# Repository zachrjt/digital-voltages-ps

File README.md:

# **Dual Fixed-Voltage Power Supply with V,I Readout**

## Background
The motivation behind this project was that in the past I have come across a need for a portable fixed-voltage 3.3V and 5V supplies. Specifically, I needed a supply that didn’t require me to set up a variable lab power supply while also being portable and rugged so that I could take it on the go.
Why did it end up taking on this *”polished”* look? I was looking to gain more SMD soldering experience and further my experience in PCB layout and schematic documentation. So, I approached this project in a more methodical, thorough-engineering manner than what I do typically for other personal projects of mine.
## Design and Construction
The main and display PCBs were captured and routed in KiCad, while the back and front enclosure panels were designed in Fusion 360. The code was, and is, written using the Arduino IDE and framework thanks only to the existence of the megaTinyCore library for 2-series attiny chips.
## Result
As seen in the picture above, the resulting power supply is certainly an *aesthetic*, but it is functional which is the most important thing. It took two PCB revisions of the main board because of wrong footprints for two resistors, and ~1 month of daily effort. There were many hours spent at my bench with an oscilloscope debugging my own oversights in the first PCB revision but I enjoyed every minute. The approach I took paid off since I've gained a lot of knowledge and experience where I wanted to, and the result is something I'm proud to share.

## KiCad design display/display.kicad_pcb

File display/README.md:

# Display Board Schematic, PCB, and Documentation

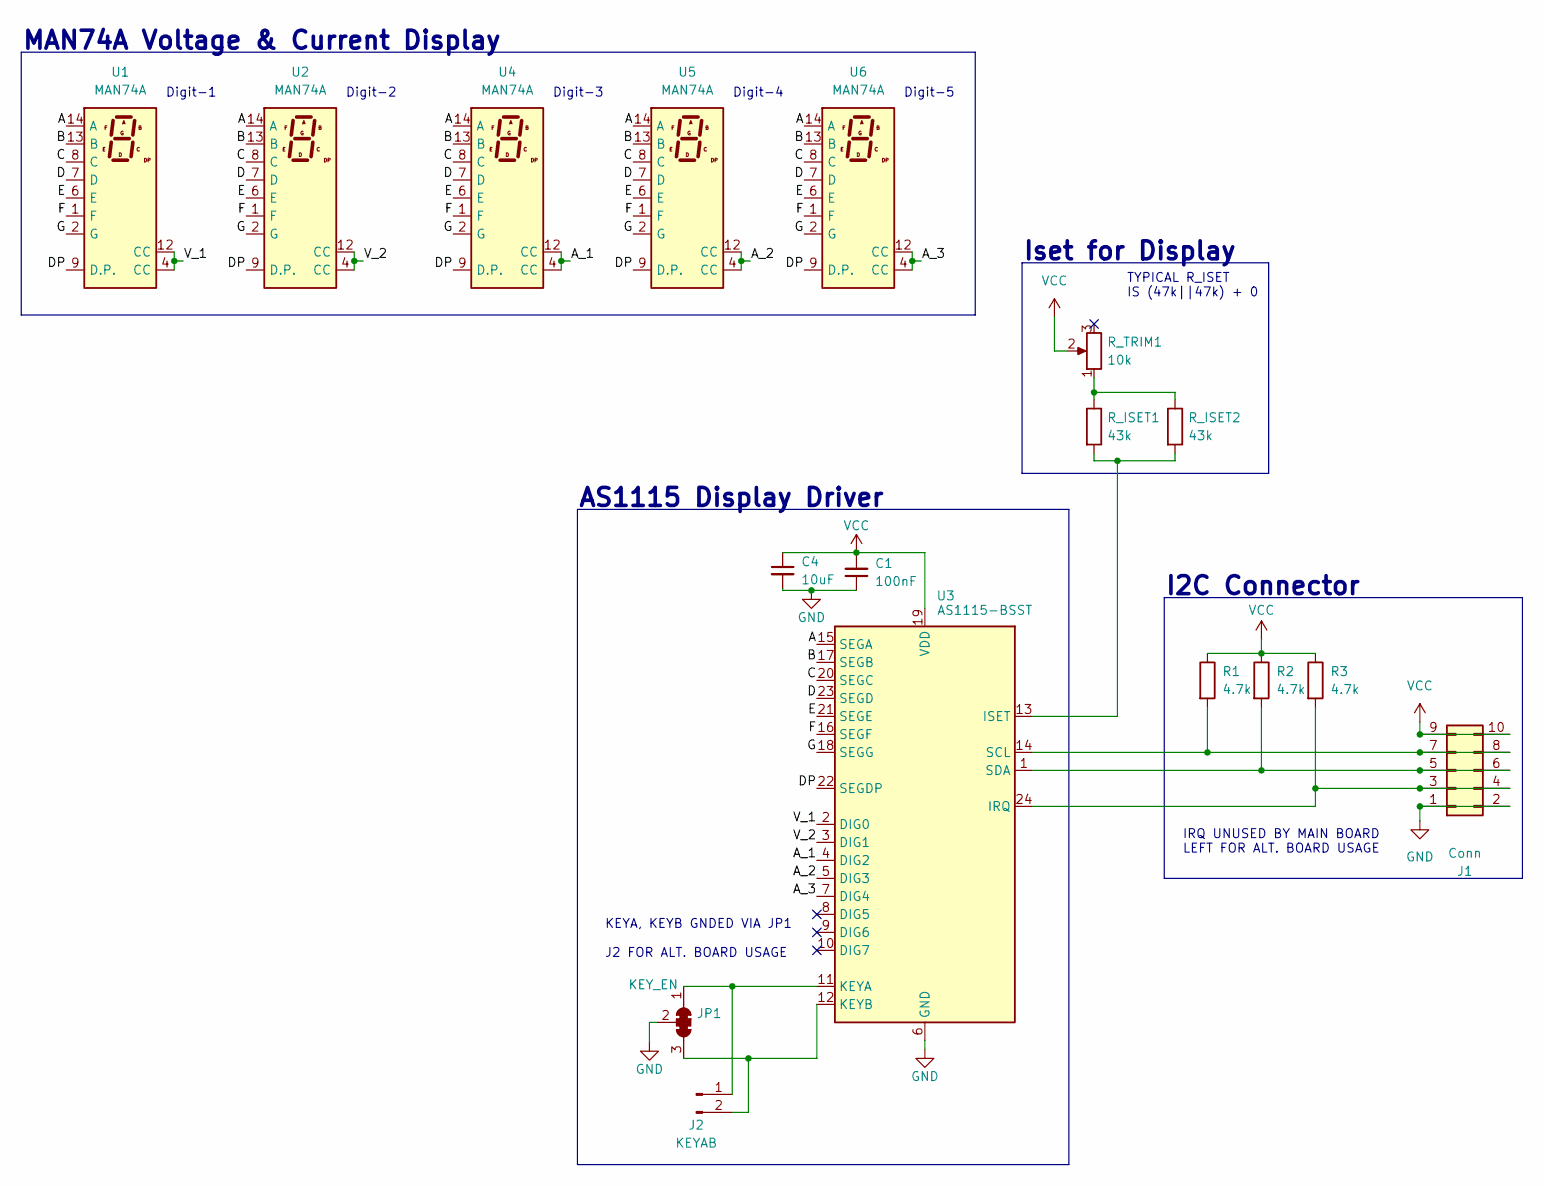
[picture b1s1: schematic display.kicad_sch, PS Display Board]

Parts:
C1: 100nF; C_0603_1608Metric_Pad1.08x0.95mm_HandSolder
C4: 10uF; C_Radial_D4.0mm_H5.0mm_P1.50mm
J1: Conn; PinHeader_2x05_P2.54mm_Horizontal
J2: KEYAB; PinHeader_1x02_P2.54mm_Vertical
JP1: KEY_EN; SolderJumper-3_P1.3mm_Open_Pad1.0x1.5mm_NumberLabels
R1, R2, R3: 4.7k; R_0603_1608Metric_Pad0.98x0.95mm_HandSolder
R_ISET1, R_ISET2: 43k; R_0603_1608Metric_Pad0.98x0.95mm_HandSolder
R_TRIM1: 10k; Potentiometer_Bourns_3362P_Vertical
U1, U2, U4, U5, U6: MAN74A
U3: AS1115-BSST; QSOP-24_3.9x8.7mm_P0.635mm

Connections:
/A: U1.14 (A), U2.14 (A), U3.15 (SEGA), U4.14 (A), U5.14 (A), U6.14 (A)
/A_1: U3.4 (DIG2), U4.4 (CC), U4.12 (CC)
/A_2: U3.5 (DIG3), U5.4 (CC), U5.12 (CC)
/A_3: U3.7 (DIG4), U6.4 (CC), U6.12 (CC)
/B: U1.13 (B), U2.13 (B), U3.17 (SEGB), U4.13 (B), U5.13 (B), U6.13 (B)
/C: U1.8 (C), U2.8 (C), U3.20 (SEGC), U4.8 (C), U5.8 (C), U6.8 (C)
/D: U1.7 (D), U2.7 (D), U3.23 (SEGD), U4.7 (D), U5.7 (D), U6.7 (D)
/DP: U1.9 (D.P.), U2.9 (D.P.), U3.22 (SEGDP), U4.9 (D.P.), U5.9 (D.P.), U6.9 (D.P.)
/E: U1.6 (E), U2.6 (E), U3.21 (SEGE), U4.6 (E), U5.6 (E), U6.6 (E)
/F: U1.1 (F), U2.1 (F), U3.16 (SEGF), U4.1 (F), U5.1 (F), U6.1 (F)
/G: U1.2 (G), U2.2 (G), U3.18 (SEGG), U4.2 (G), U5.2 (G), U6.2 (G)
/V_1: U1.4 (CC), U1.12 (CC), U3.2 (DIG0)
/V_2: U2.4 (CC), U2.12 (CC), U3.3 (DIG1)
GND: C1.1, C4.2, J1.1, J1.2, JP1.2 (C), U3.6 (GND)
unnamed: J2.1, JP1.1 (A), U3.11 (KEYA)
unnamed: J2.2, JP1.3 (B), U3.12 (KEYB)
unnamed: J1.7, J1.8, R1.2, U3.14 (SCL)
unnamed: J1.5, J1.6, R2.2, U3.1 (SDA)
unnamed: J1.3, J1.4, R3.2, U3.24 (IRQ)
unnamed: R_ISET1.1, R_ISET2.1, R_TRIM1.1
unnamed: R_ISET1.2, R_ISET2.2, U3.13 (ISET)
VCC: C1.2, C4.1, J1.9, J1.10, R1.1, R2.1, R3.1, R_TRIM1.2, U3.19 (VDD)

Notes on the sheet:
TYPICAL R_ISET IS (47k||47k) + 0
I2C Connector
Digit-3
AS1115 Display Driver
KEYA, KEYB GNDED VIA JP1 J2 FOR ALT. BOARD USAGE
Digit-4
Iset for Display
Digit-5
Digit-2
MAN74A Voltage & Current Display
Digit-1
IRQ UNUSED BY MAIN BOARD LEFT FOR ALT. BOARD USAGE

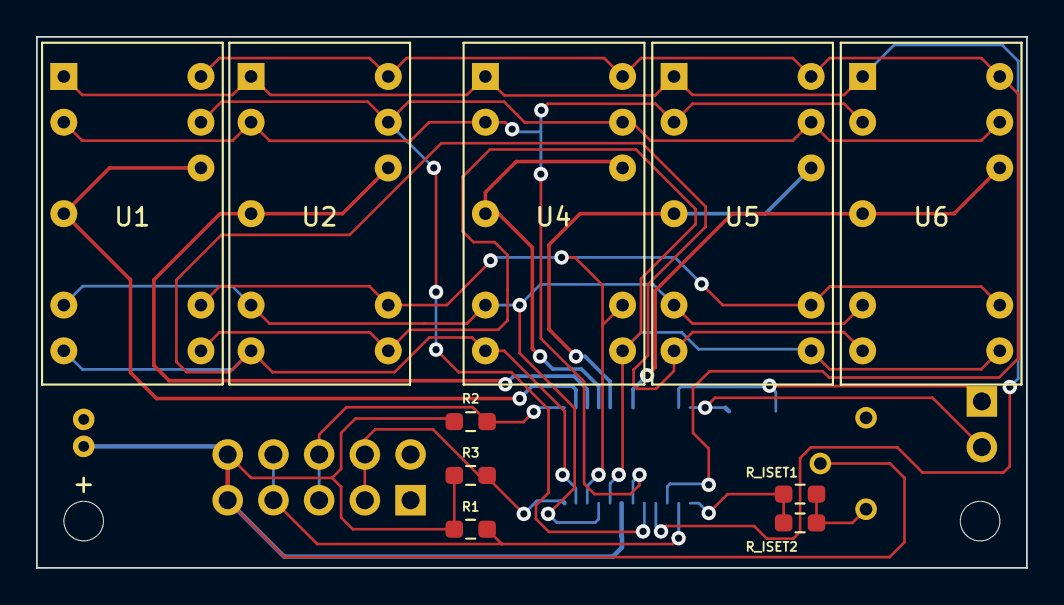
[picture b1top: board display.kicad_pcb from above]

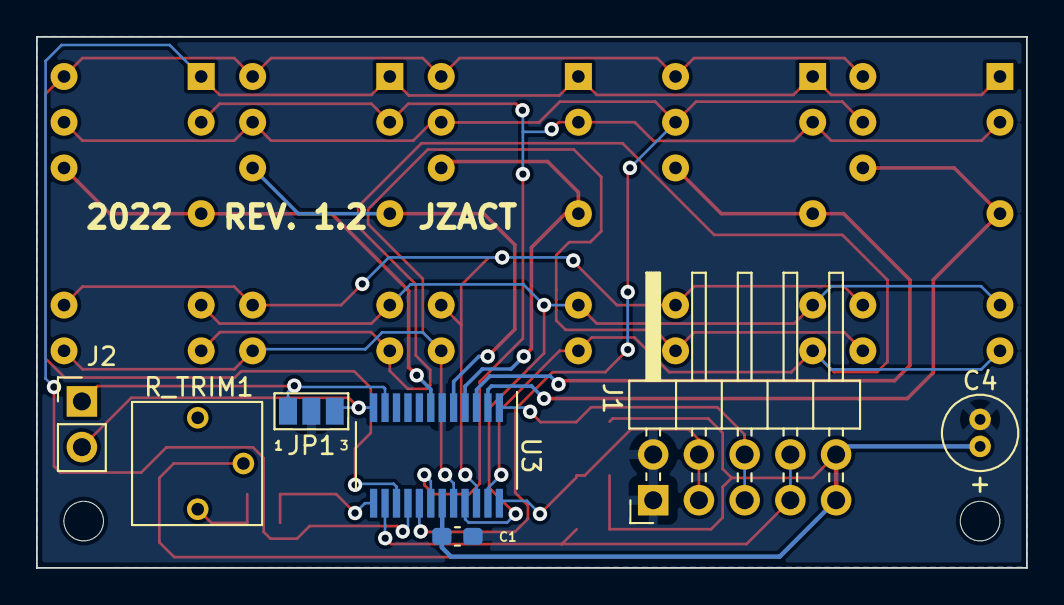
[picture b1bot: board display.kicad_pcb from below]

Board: 2 copper layers, 55.0 x 29.5 mm, 20 parts (7 on the bottom side), 22 nets.

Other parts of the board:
M1, M3: MountingHole_2.2mm_M2
M4: display_cutout

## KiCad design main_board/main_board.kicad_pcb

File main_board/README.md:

# Main Board Schematic, PCB, and Documentation

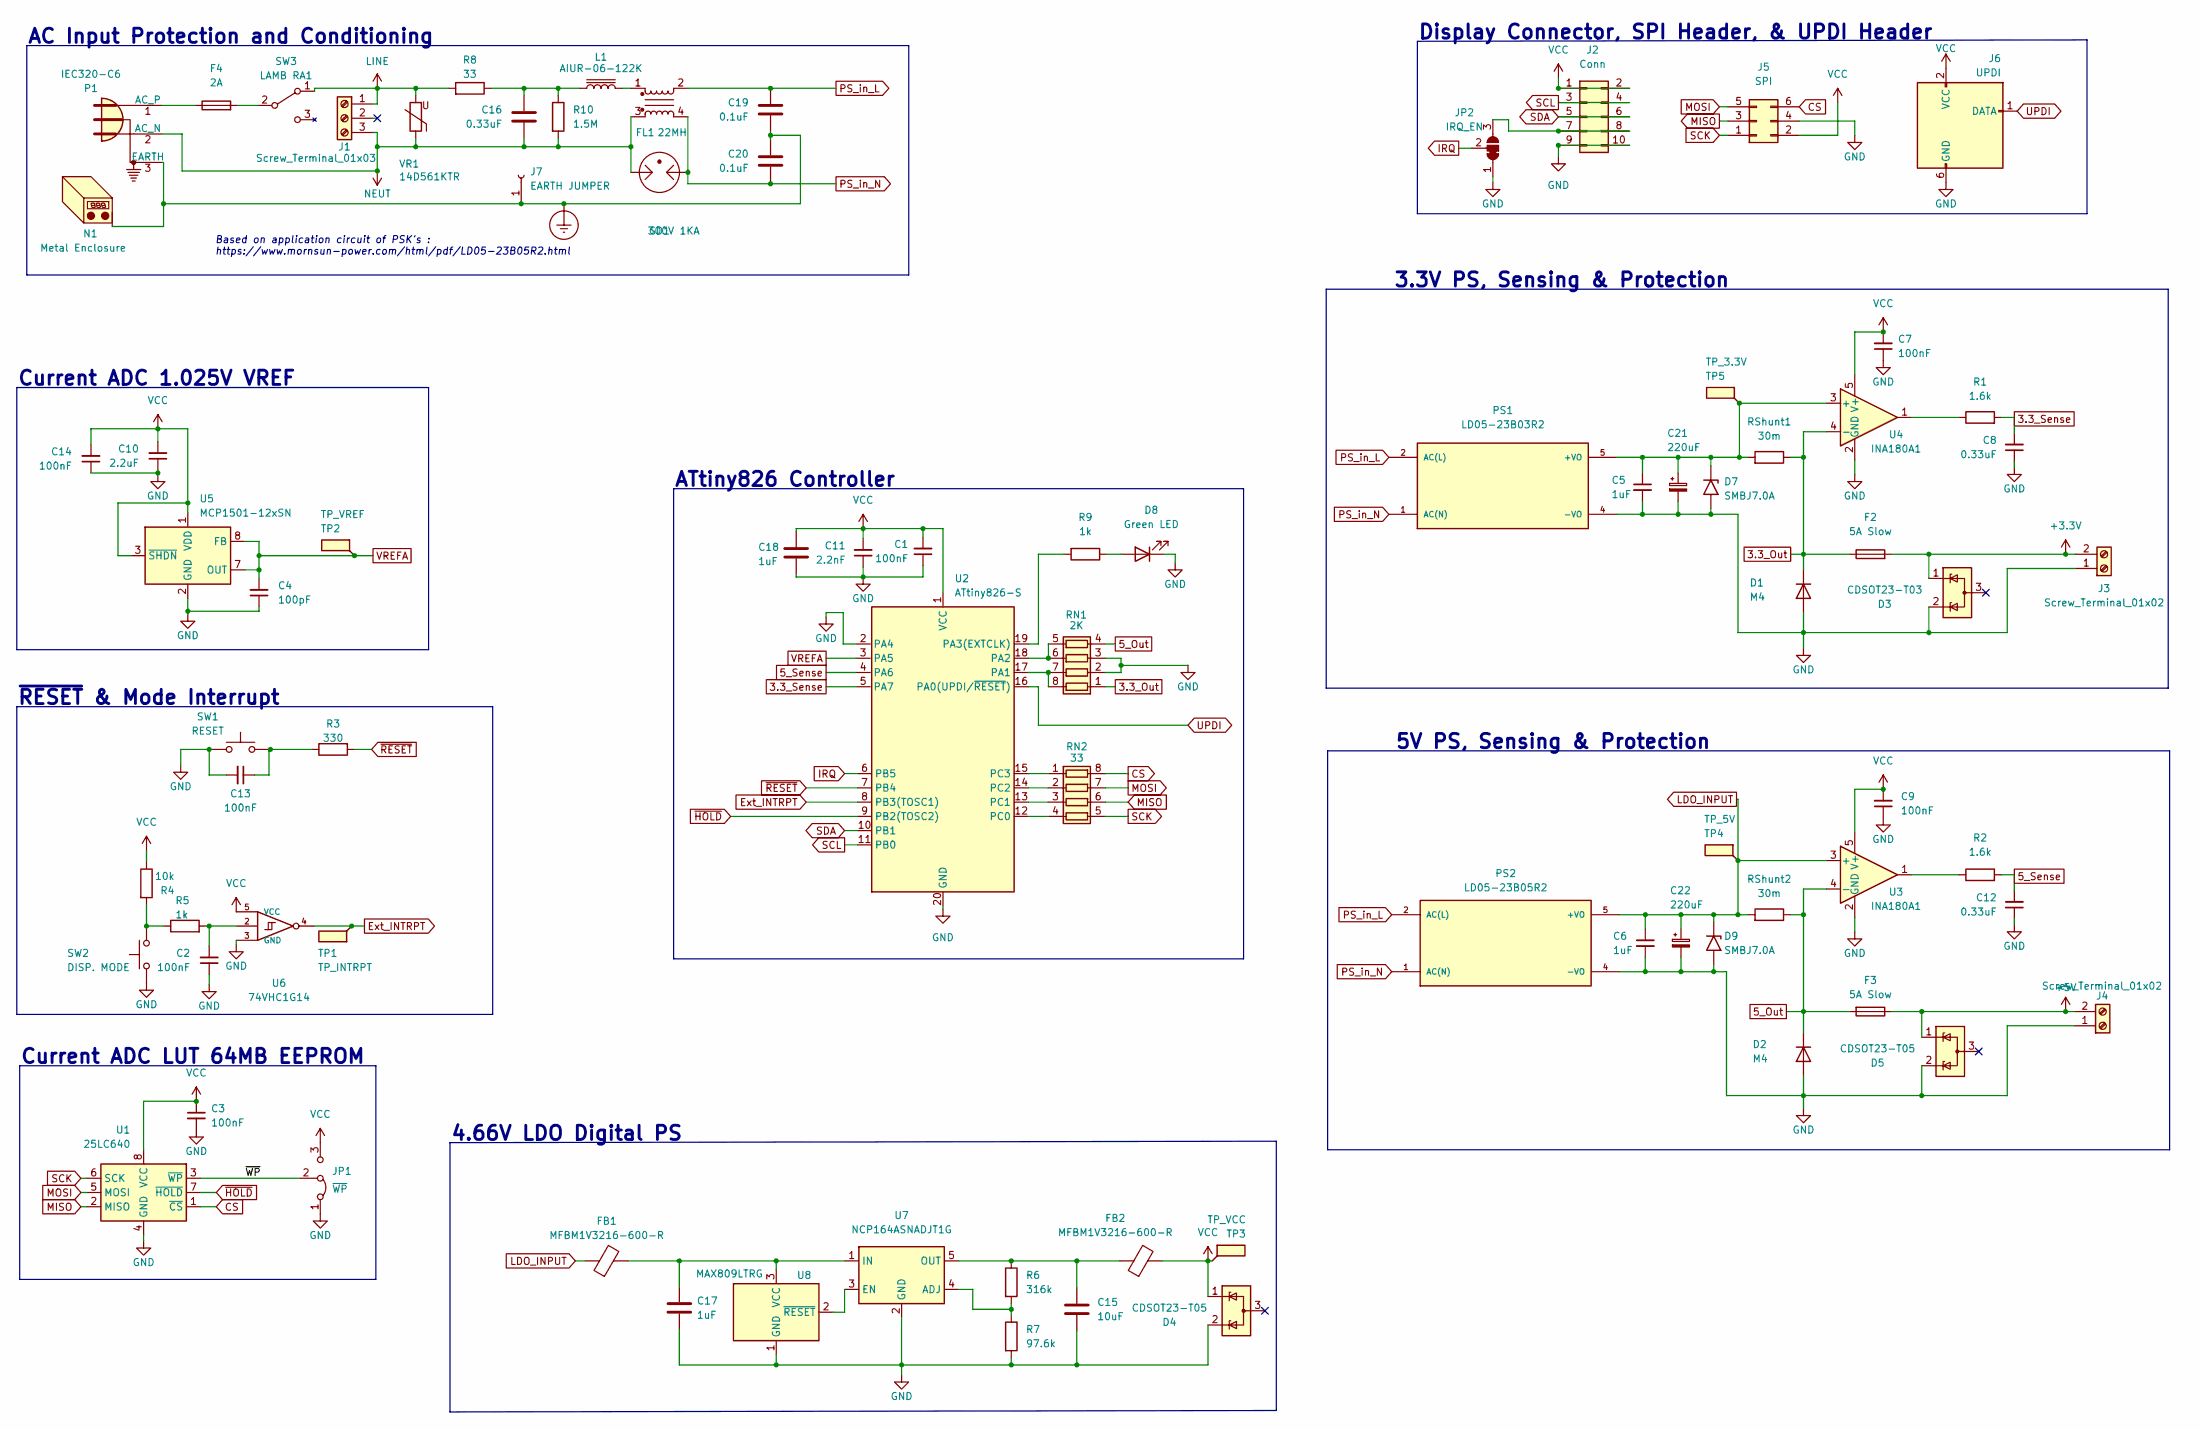
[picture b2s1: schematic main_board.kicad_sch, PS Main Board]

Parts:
C1, C3, C7, C9, C14: 100nF; C_1206_3216Metric_Pad1.33x1.80mm_HandSolder
C2, C13: 100nF; C_0805_2012Metric_Pad1.18x1.45mm_HandSolder
C4: 100pF; C_0603_1608Metric_Pad1.08x0.95mm_HandSolder
C5, C6: 1uF; C320C105K5R5TA
C8, C12: 0.33uF; C_1206_3216Metric_Pad1.33x1.80mm_HandSolder
C10: 2.2uF; C_0805_2012Metric_Pad1.18x1.45mm_HandSolder
C11: 2.2nF; C_0805_2012Metric_Pad1.18x1.45mm_HandSolder
C15: 10uF; C_0805_2012Metric_Pad1.18x1.45mm_HandSolder
C16: 0.33uF; C_Rect_L18.0mm_W8.0mm_P15.00mm_FKS3_FKP3
C17, C18: 1uF; C_0805_2012Metric_Pad1.18x1.45mm_HandSolder
C19, C20: 0.1uF; C_Rect_L18.0mm_W6.0mm_P15.00mm_FKS3_FKP3
C21, C22: 220uF; C_Radial_D6.3mm_H11.0mm_P2.50mm
D1, D2: M4; D_SMB
D3: CDSOT23-T03; SOT-23
D4, D5: CDSOT23-T05; SOT-23
D7, D9: SMBJ7.0A; D_SMB
D8: Green LED; LED_0805_2012Metric_Pad1.15x1.40mm_HandSolder
F2, F3: 5A Slow; Fuse_1206_3216Metric_Pad1.42x1.75mm_HandSolder
F4: 2A
FB1, FB2: MFBM1V3216-600-R; L_1206_3216Metric_Pad1.42x1.75mm_HandSolder
FL1: 22MH; Choke_Schaffner_RN218-04-12.5x18.0mm
GD1: 300V 1KA; 2035-GDT
J1: Screw_Terminal_01x03; TerminalBlock_Phoenix_MKDS-1,5-3-5.08_1x03_P5.08mm_Horizont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
J2: Conn; PinHeader_2x05_P2.54mm_Vertical
J3, J4: Screw_Terminal_01x02; TerminalBlock_Phoenix_MKDS-1,5-2-5.08_1x02_P5.08mm_Horizont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
J5: SPI; PinHeader_2x03_P2.54mm_Vertical
J6: UPDI; PinHeader_2x03_P2.54mm_Vertical
J7: EARTH JUMPER; PinHeader_1x01_P2.54mm_Vertical
JP1: ~{WP}; PinHeader_1x03_P1.27mm_Vertical
JP2: IRQ_EN; SolderJumper-3_P1.3mm_Open_RoundedPad1.0x1.5mm_NumberLabels
L1: AIUR-06-122K; AIUR-06
N1: Metal Enclosure
P1: IEC320-C6
PS1: LD05-23B03R2; CONV_LD05-23B03R2; PARTREV 2020.06.30-A/2
PS2: LD05-23B05R2; CONV_LD05-23B05R2; PARTREV 2020.06.30-A/2
R1, R2: 1.6k; R_1206_3216Metric_Pad1.30x1.75mm_HandSolder
R3: 330; R_0805_2012Metric_Pad1.20x1.40mm_HandSolder
R4: 10k; R_0805_2012Metric_Pad1.20x1.40mm_HandSolder
R5, R9: 1k; R_0805_2012Metric_Pad1.20x1.40mm_HandSolder
R6: 316k; R_0805_2012Metric_Pad1.20x1.40mm_HandSolder
R7: 97.6k; R_0805_2012Metric_Pad1.20x1.40mm_HandSolder
R8: 33; R_Radial_Power_L13.0mm_W9.0mm_P5.00mm
R10: 1.5M; R_Axial_DIN0207_L6.3mm_D2.5mm_P10.16mm_Horizontal
RN1: 2K; R_Array_Convex_4x0603
RN2: 33; R_Array_Convex_4x0603
RShunt1, RShunt2: 30m; R_0805_2012Metric_Pad1.20x1.40mm_HandSolder
SW1: RESET; SW_SPST_CK_RS282G05A3
SW2: DISP. MODE; PinHeader_1x02_P2.54mm_Vertical
SW3: LAMB RA1
TP1: TP_INTRPT; TestPoint_Pad_D1.0mm
TP2: TP_VREF; TestPoint_Pad_D1.0mm
TP3: TP_VCC; TestPoint_Pad_D1.0mm
TP4: TP_5V; TestPoint_Pad_D1.0mm
TP5: TP_3.3V; TestPoint_Pad_D1.0mm
U1: 25LC640; SOIC-8_3.9x4.9mm_P1.27mm
U2: ATtiny826-S; SOIC-20W_7.5x12.8mm_P1.27mm
U3, U4: INA180A1; SOT-23-5_HandSoldering
U5: MCP1501-12xSN; SOIC-8_3.9x4.9mm_P1.27mm
U6: 74VHC1G14; SOT-23-5_HandSoldering
U7: NCP164ASNADJT1G; TSOP-5
U8: MAX809LTRG; SOT-23
VR1: 14D561KTR; RV_Disc_D16.5mm_W6.7mm_P7.5mm

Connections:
3.3_Out: D1.1 (K), F2.1, RN1.1 (R1.1), RShunt1.1, U4.4 (-)
3.3_Sense: C8.2, R1.2, U2.5 (PA7)
5_Out: D2.1 (K), F3.2, RN1.4 (R4.1), RShunt2.1, U3.4 (-)
5_Sense: C12.2, R2.2, U2.4 (PA6)
+3V3: D3.1 (K), F2.2, J3.2
+5V: D5.1 (K), F3.1, J4.2
/~WP: JP1.2 (C), U1.3 (~WP)
CS: J5.6, RN2.8 (R1.2), U1.1 (~CS)
Earth_Protective: C19.1, C20.2, J7.1, N1.1, P1.3 (EARTH)
Ext_INTRPT: TP1.1, U2.8 (PB3(TOSC1)), U6.4
GND: C1.1, C2.1, C3.2, C4.1, C5.2, C6.2, C7.1, C8.1, C9.1, C10.1, C11.1, C12.1, C13.2, C14.1, C15.2, C17.2, C18.2, C21.2, C22.2, D1.2 (A), D2.2 (A), D3.2 (K), D4.2 (K), D5.2 (K), D7.2 (A2), D8.1 (K), D9.2 (A2), J2.9, J2.10, J3.1, J4.1, J5.4, J6.6 (GND), JP1.1 (A), JP2.1 (A), PS1.4 (-VO), PS2.4 (-VO), R7.2, RN1.2 (R2.1), RN1.3 (R3.1), SW1.1, SW2.1, U1.4 (GND), U2.2 (PA4), U2.20 (GND), U3.2 (GND), U4.2 (GND), U5.2 (GND), U5.4 (GND), U5.5 (GND), U5.6 (GND), U6.3 (GND), U7.2 (GND), U8.1 (GND)
IRQ: JP2.2 (C), U2.6 (PB5)
LDO_INPUT: C6.1, C22.1, D9.1 (A1), FB1.1, PS2.5 (+VO), RShunt2.2, TP4.1, U3.3 (+)
LINE: J1.1, R8.2, SW3.1 (A), VR1.2
MISO: J5.3, RN2.6 (R3.2), U1.2 (MISO)
MOSI: J5.5, RN2.7 (R2.2), U1.5 (MOSI)
NEUT: C16.1, FL1.3, GD1.2, J1.3, P1.2 (AC_N), R10.2, VR1.1
unnamed: C2.2, R5.2, U6.2
unnamed: C15.1, FB2.1, R6.1, U7.5 (OUT)
unnamed: C16.2, L1.1, R8.1, R10.1
unnamed: C17.1, FB1.2, U7.1 (IN), U8.3 (VCC)
unnamed: C5.1, C21.1, D7.1 (A1), PS1.5 (+VO), RShunt1.2, TP5.1, U4.3 (+)
unnamed: D8.2 (A), R9.1
unnamed: F4.1, P1.1 (AC_P)
unnamed: F4.2, SW3.2 (B)
unnamed: FL1.1, L1.2
unnamed: J2.7, J2.8, JP2.3 (B)
unnamed: R1.1, U4.1
unnamed: R2.1, U3.1
unnamed: C13.1, R3.1, SW1.2
unnamed: R4.2, R5.1, SW2.2
unnamed: R6.2, R7.1, U7.4 (ADJ)
unnamed: R9.2, U2.19 (PA3(EXTCLK))
unnamed: RN1.5 (R4.2), RN1.6 (R3.2), U2.18 (PA2)
unnamed: RN1.7 (R2.2), RN1.8 (R1.2), U2.17 (PA1)
unnamed: RN2.1 (R1.1), U2.15 (PC3)
unnamed: RN2.2 (R2.1), U2.14 (PC2)
unnamed: RN2.3 (R3.1), U2.13 (PC1)
unnamed: RN2.4 (R4.1), U2.12 (PC0)
unnamed: U7.3 (EN), U8.2 (~RESET)
PS_in_L: C19.2, FL1.2, PS1.2 (AC(L)), PS2.2 (AC(L))
PS_in_N: C20.1, FL1.4, GD1.1, PS1.1 (AC(N)), PS2.1 (AC(N))
SCK: J5.1, RN2.5 (R4.2), U1.6 (SCK)
SCL: J2.3, J2.4, U2.11 (PB0)
SDA: J2.5, J2.6, U2.10 (PB1)
UPDI: J6.1 (DATA), U2.16 (PA0(UPDI/~RESET))
VCC: C1.2, C3.1, C7.2, C9.2, C10.2, C11.2, C14.2, C18.1, D4.1 (K), FB2.2, J2.1, J2.2, J5.2, J6.2 (VCC), JP1.3 (B), R4.1, TP3.1, U1.8 (VCC), U2.1 (VCC), U3.5 (V+), U4.5 (V+), U5.1 (VDD), U5.3 (~SHDN), U6.5 (VCC)
VREFA: C4.2, TP2.1, U2.3 (PA5), U5.7 (OUT), U5.8 (FB)
~HOLD: U1.7 (~HOLD), U2.9 (PB2(TOSC2))
~RESET: R3.2, U2.7 (PB4)

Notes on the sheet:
Display Connector, SPI Header, & UPDI Header
4.66V LDO Digital PS
~{RESET} & Mode Interrupt
Current ADC LUT 64MB EEPROM
Current ADC 1.025V VREF
AC Input Protection and Conditioning
5V PS, Sensing & Protection
Based on application circuit of PSK's : https://www.mornsun-power.com/html/pdf/LD05-23B05R2.html
3.3V PS, Sensing & Protection
ATtiny826 Controller

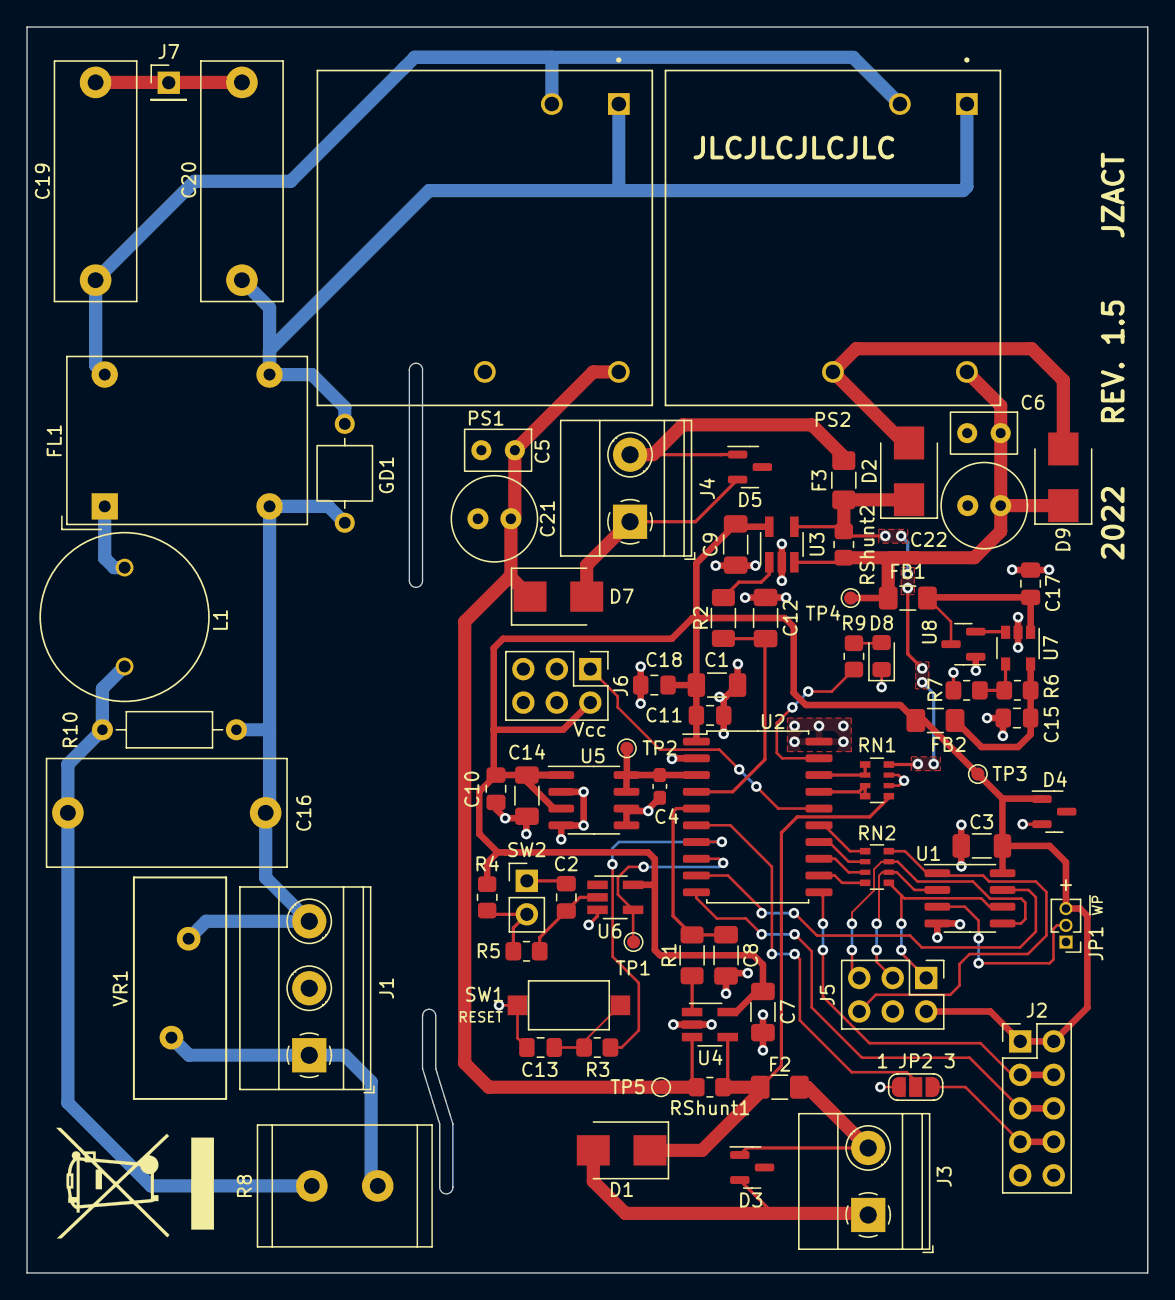
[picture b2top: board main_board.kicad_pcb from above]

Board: 2 copper layers, 85.0 x 94.5 mm, 78 parts (0 on the bottom side), 48 nets.

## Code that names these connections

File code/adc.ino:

#include "adc.h"
/*
 * (TODO)
 *  -Transistion ADC code over to the megaTinycore non-standard functions for 
 *  hardware based 8 & 12bit burst sampling.
 *    (https://github.com/SpenceKonde/megaTinyCore/blob/master/megaavr/extras/Ref_Analog.md)
 *  -Create dibble-dabble or lut table conversion of ADC samples (depends on transistioned ADC code).
 *    Current adc sample conversion is HIGHLY inefficient (int32->string->int8).
*/
 
void Voltage_ADCReading()
{
  int temp_adc_value = 0x00;
  uint8_t input_pin = (value_state) ? PIN_PA1 : PIN_PA2; //False(default) = 3.3V, True = 5V
  
  analogReference(INTERNAL4V096);
  analogReadResolution(10);
  analogSampleDuration(10);
  delay(1);
  
  for (int i = 0x00; i < 0xFF; i++)
  {
    temp_adc_value = analogRead(input_pin);
    voltage = voltage + (temp_adc_value * (4.096/1024));
  }
  voltage = voltage/(128);
  
  disp_volt = String(voltage, 3);
  display_data[0] = (uint8_t)(disp_volt[0]) - 0x30;
  display_data[1] = (uint8_t)(disp_volt[2]) - 0x30;
  return;
}



void Current_ADCReading()
{
  int temp_adc_value = 0x00;
  uint8_t input_pin = (value_state) ? PIN_PA7 : PIN_PA6; //False(default) = 3.3V, True = 5V
  
  analogReference(EXTERNAL);
  analogReadResolution(12);
  analogSampleDuration(10);
  delay(1);
  
  for (int i = 0x00; i < 0xFF; i++)
  {
    temp_adc_value = analogRead(input_pin);
    current = current + (temp_adc_value * (2.08333333/4096));
  }
  current = current/(256);
  
  disp_amp = String(current, 4);
  display_data[2] = (uint8_t)(disp_amp[0]) - 0x30;
  display_data[3] = (uint8_t)(disp_amp[2]) - 0x30;
  display_data[4] = (uint8_t)(disp_amp[3]) - 0x30;
  return;
}


//legacy code
/*
void Voltage_ADCInitialize()
{
  //
  //Calibrate offset
  ADC0.CTRLA = 0x21; // Not run in standby sleep mode, low latency EN, ADC EN
  ADC0.CTRLB = 0x00; // Lowest prescale (div 2)
  ADC0.CTRLC = 0x07; // Internal 4.096V reference
  ADC0.CTRLE = 0x0; // 
  ADC0.CTRLF = 0x00;
  ADC0.CTRLD = 0x00; // Disable window comparator
  ADC0.INTCTRL = 0x01; // EN result ready interrupt
  ADC0.MUXPOS = 0x30; // NO PGA, Internal GND Connection
  delay(1);
  analogReference(INTERNAL4V096); //Requires VDD > 4.596V
  analogReadResolution(10);
  analogSampleDuration(6);
  return;
}

void Current_ADCInitialize()
{
  return;
}
*/

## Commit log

2022-10-04 Added Rev1.1 display board and Rev1.4 main board KiCad projects
2022-10-05 Added front and back panel enclosure stp and drawing files
2023-01-03 Added initial code base, improved and fixed hardware up to Rev 1.5/1.2 for the main and display boards respectively, and add pictures of (mostly) complete result
